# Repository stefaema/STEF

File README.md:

# STEF
Film Transport and Scanning System / Sistema de Transporte y Escaneo Fílmico

## The shells

One `flake.nix`, at the root, and one `flake.lock`. Every module declares what
it needs in its own `module.nix`, as data rather than as an assembled shell, and
the root flake turns those declarations into shells:

```bash
nix develop            # the editor shell
nix develop .#gui      # one module
```

The editor shell is the union: one interpreter carrying every Python import in
the tree, plus `ruff`, `basedpyright` and `clangd`.

A `module.nix` returns an attribute set, every field optional:

| field | what it declares |
| --- | --- |
| `description` | the line `nix eval .#modules.<system>` prints |
| `systems` | where the module builds, both Linux architectures by default |
| `python` | `ps: [ ... ]`, the interpreter's packages |
| `packages` | everything else on `PATH` |
| `env` | variables the shell exports |
| `pythonOverlay` | packages nixpkgs does not carry, added to the interpreter |
| `shell` | a shell taken whole from elsewhere, which `firmware` does |

The interpreter is 3.13, fixed there by `rig`'s CAD wheels being `cp313`.

Every shell exports `STEF_HOME`, pointing at `local/`. `shared.paths` reads it
to decide where config, state and logs go, so a shell that left it unset would
write the log file somewhere nobody thinks to look.

Updating nixpkgs is `nix flake update`, once, at the root.

## Modules

A directory holding a `module.nix` is a module; one without it only groups the
modules below it. The root flake and `ci_cd/discovery.py` walk that same rule,
so one file both declares a module's toolchain and makes it a module. `python -m
ci_cd.run --list` prints what discovery found.

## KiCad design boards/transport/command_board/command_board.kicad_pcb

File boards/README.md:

# Boards
This part of the project will explore the hardware. Specifically, It holds the KiCAD project and Gerber files to both the carrier and driver board.

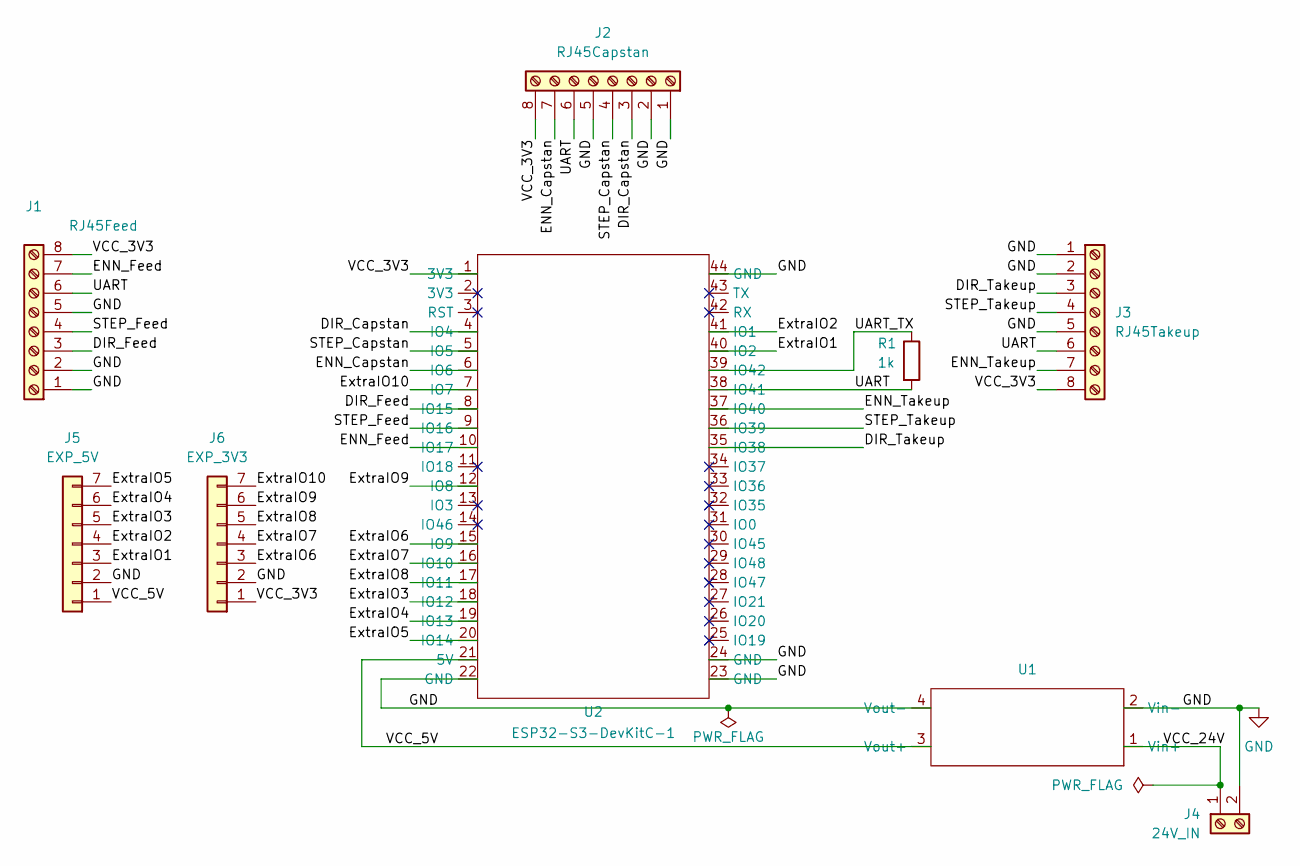
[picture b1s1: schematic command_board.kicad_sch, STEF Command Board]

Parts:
J1: RJ45Feed; PhoenixContact_MC_1,5_8-G-3.5_1x08_P3.50mm_Horizontal
J2: RJ45Capstan; PhoenixContact_MC_1,5_8-G-3.5_1x08_P3.50mm_Horizontal
J3: RJ45Takeup; PhoenixContact_MC_1,5_8-G-3.5_1x08_P3.50mm_Horizontal
J4: 24V_IN; TerminalBlock_RND_205-00287_1x02_P5.08mm_Horizontal
J5: EXP_5V; PinHeader_1x07_P2.54mm_Vertical
J6: EXP_3V3; PinHeader_1x07_P2.54mm_Vertical
R1: 1k; R_Axial_DIN0207_L6.3mm_D2.5mm_P10.16mm_Horizontal
U1: Buck_LM2596; Buck_LM2596_Socketed_2x02
U2: ESP32-S3-DevKitC-1; ESP32-S3-DevKitC-1_Socketed_2x22

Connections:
/DIR_Capstan: J2.3, U2.4 (IO4)
/DIR_Feed: J1.3, U2.8 (IO15)
/DIR_Takeup: J3.3, U2.35 (IO38)
/ENN_Capstan: J2.7, U2.6 (IO6)
/ENN_Feed: J1.7, U2.10 (IO17)
/ENN_Takeup: J3.7, U2.37 (IO40)
/ExtraIO1: J5.3, U2.40 (IO2)
/ExtraIO2: J5.4, U2.41 (IO1)
/ExtraIO3: J5.5, U2.18 (IO12)
/ExtraIO4: J5.6, U2.19 (IO13)
/ExtraIO5: J5.7, U2.20 (IO14)
/ExtraIO6: J6.3, U2.15 (IO9)
/ExtraIO7: J6.4, U2.16 (IO10)
/ExtraIO8: J6.5, U2.17 (IO11)
/ExtraIO9: J6.6, U2.12 (IO8)
/ExtraIO10: J6.7, U2.7 (IO7)
/STEP_Capstan: J2.4, U2.5 (IO5)
/STEP_Feed: J1.4, U2.9 (IO16)
/STEP_Takeup: J3.4, U2.36 (IO39)
/UART: J1.6, J2.6, J3.6, R1.2, U2.38 (IO41)
/UART_TX: R1.1, U2.39 (IO42)
/VCC_3V3: J1.8, J2.8, J3.8, J6.1, U2.1 (3V3)
/VCC_5V: J5.1, U1.3 (Vout+), U2.21 (5V)
/VCC_24V: J4.1, U1.1 (Vin+)
GND: J1.1, J1.2, J1.5, J2.1, J2.2, J2.5, J3.1, J3.2, J3.5, J4.2, J5.2, J6.2, U1.2 (Vin-), U1.4 (Vout-), U2.22 (GND), U2.23 (GND), U2.24 (GND), U2.44 (GND)

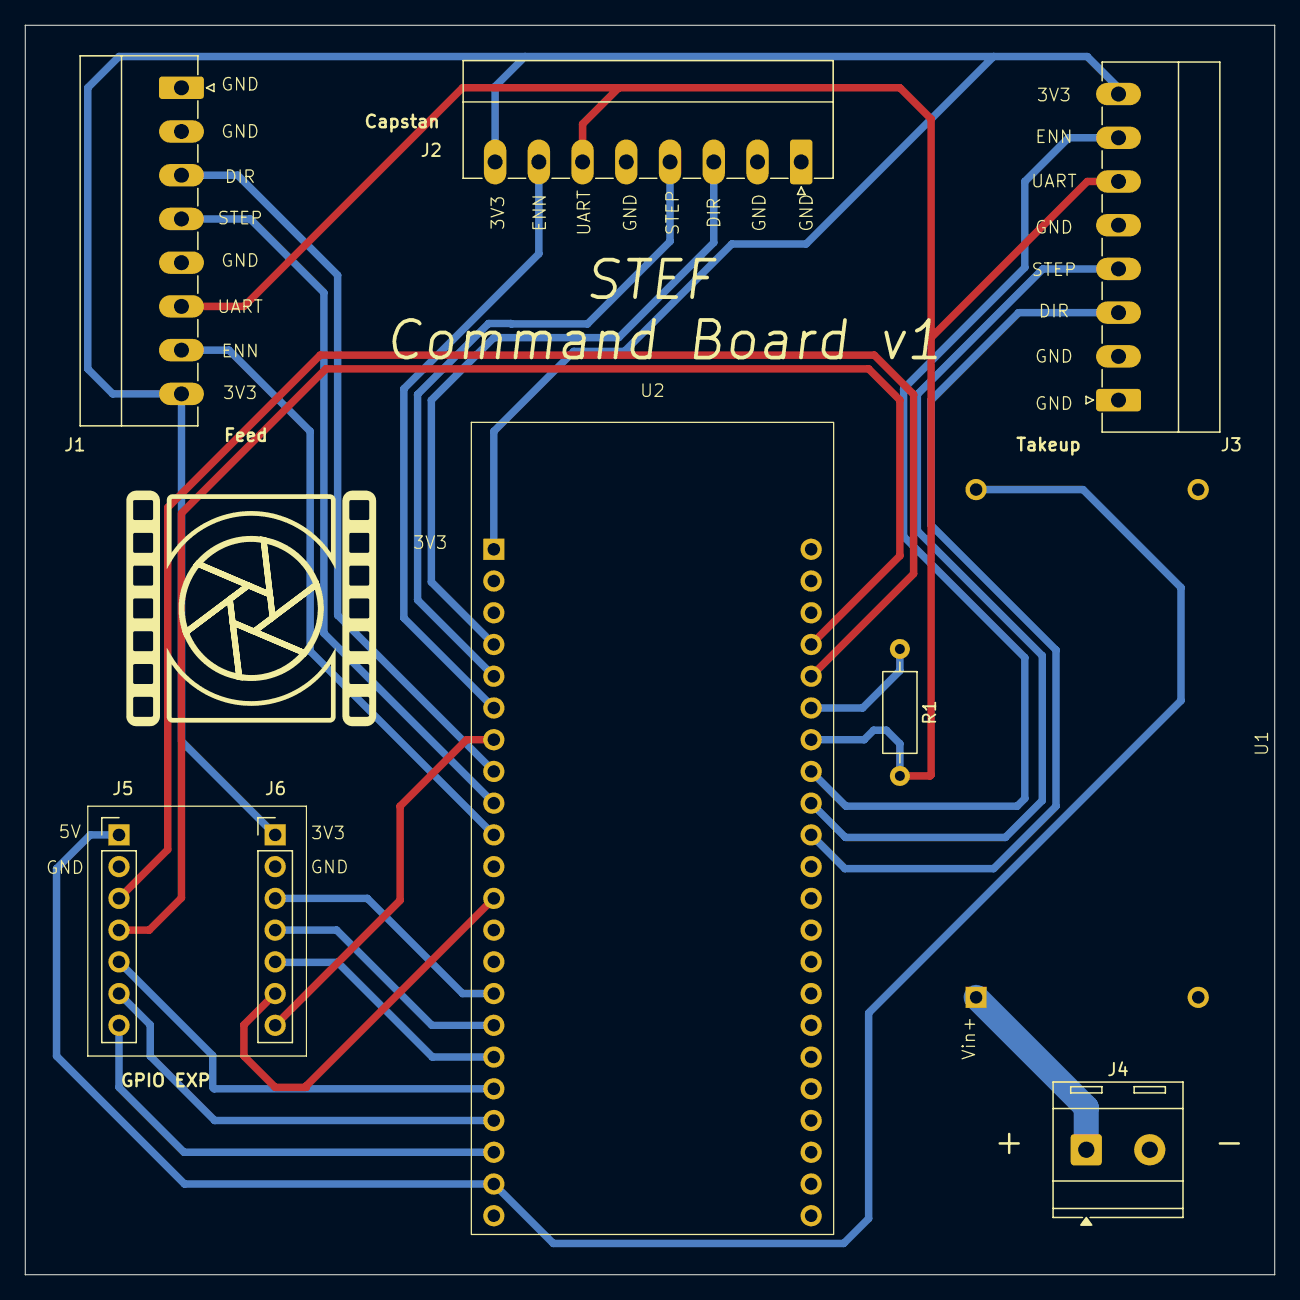
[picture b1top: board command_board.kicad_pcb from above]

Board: 2 copper layers, 100.0 x 100.0 mm, 9 parts (0 on the bottom side), 25 nets.

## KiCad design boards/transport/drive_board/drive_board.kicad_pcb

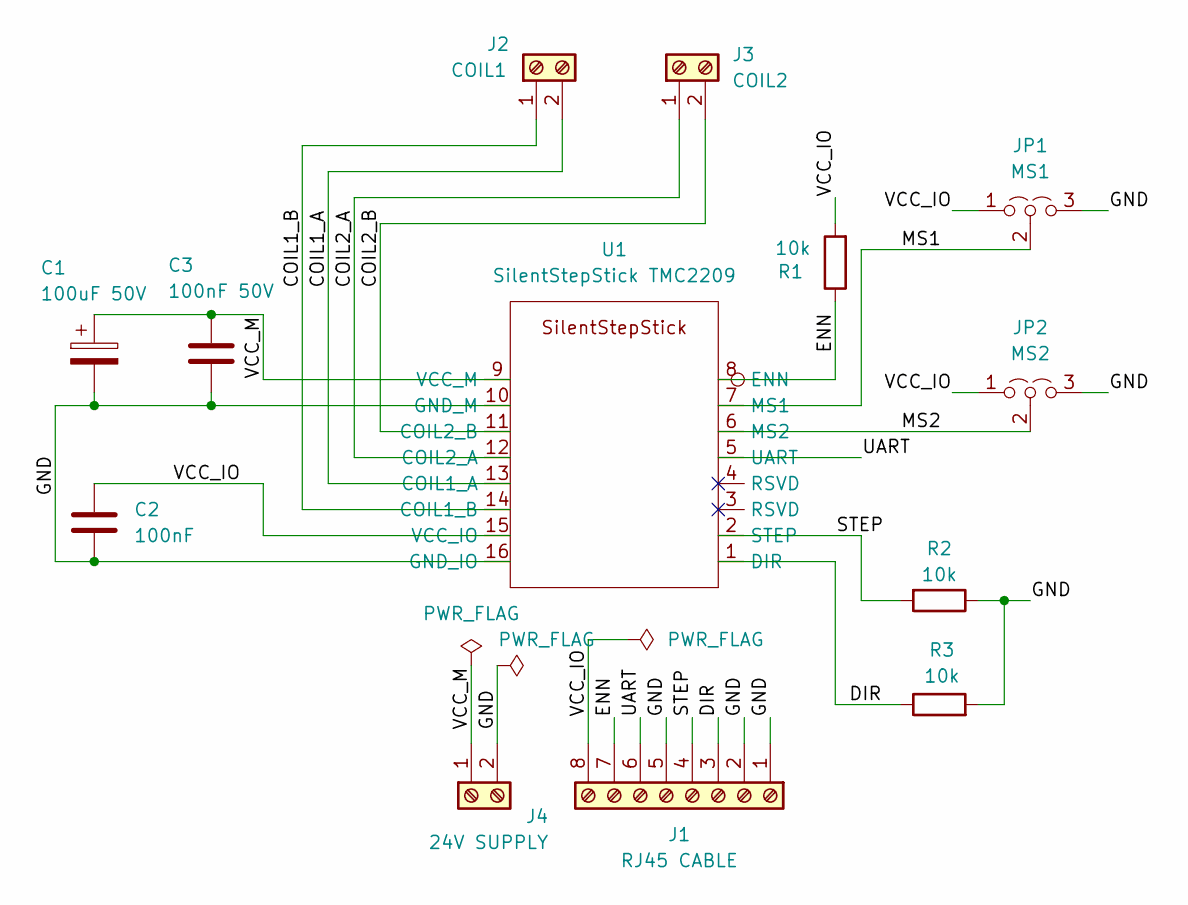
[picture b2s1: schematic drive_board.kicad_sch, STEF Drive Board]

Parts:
C1: 100uF 50V; CP_Radial_D8.0mm_P5.00mm
C2: 100nF; C_Disc_D7.0mm_W2.5mm_P5.00mm
C3: 100nF 50V; C_Disc_D7.0mm_W2.5mm_P5.00mm
J1: RJ45 CABLE; PhoenixContact_MC_1,5_8-G-3.5_1x08_P3.50mm_Horizontal
J2: COIL1; TerminalBlock_RND_205-00287_1x02_P5.08mm_Horizontal
J3: COIL2; TerminalBlock_RND_205-00287_1x02_P5.08mm_Horizontal
J4: 24V SUPPLY; TerminalBlock_RND_205-00287_1x02_P5.08mm_Horizontal
JP1: MS1; PinHeader_1x03_P2.54mm_Vertical
JP2: MS2; PinHeader_1x03_P2.54mm_Vertical
R1, R2, R3: 10k; R_Axial_DIN0207_L6.3mm_D2.5mm_P10.16mm_Horizontal
U1: SilentStepStick TMC2209; SilentStepStick_Socketed_2x08

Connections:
/COIL1_A: J2.2, U1.13 (COIL1_A)
/COIL1_B: J2.1, U1.14 (COIL1_B)
/COIL2_A: J3.1, U1.12 (COIL2_A)
/COIL2_B: J3.2, U1.11 (COIL2_B)
/DIR: J1.3, R3.1, U1.1 (DIR)
/ENN: J1.7, R1.1, U1.8 (ENN)
/GND: C1.2, C2.2, C3.2, J1.1, J1.2, J1.5, J4.2, JP1.3 (B), JP2.3 (B), R2.1, R3.2, U1.10 (GND_M), U1.16 (GND_IO); also elsewhere on the board
/MS1: JP1.2 (C), U1.7 (MS1); also elsewhere on the board
/MS2: JP2.2 (C), U1.6 (MS2)
/STEP: J1.4, R2.2, U1.2 (STEP)
/UART: J1.6, U1.5 (UART)
/VCC_IO: C2.1, J1.8, JP1.1 (A), JP2.1 (A), R1.2, U1.15 (VCC_IO); also elsewhere on the board
/VCC_M: C1.1, C3.1, J4.1, U1.9 (VCC_M)

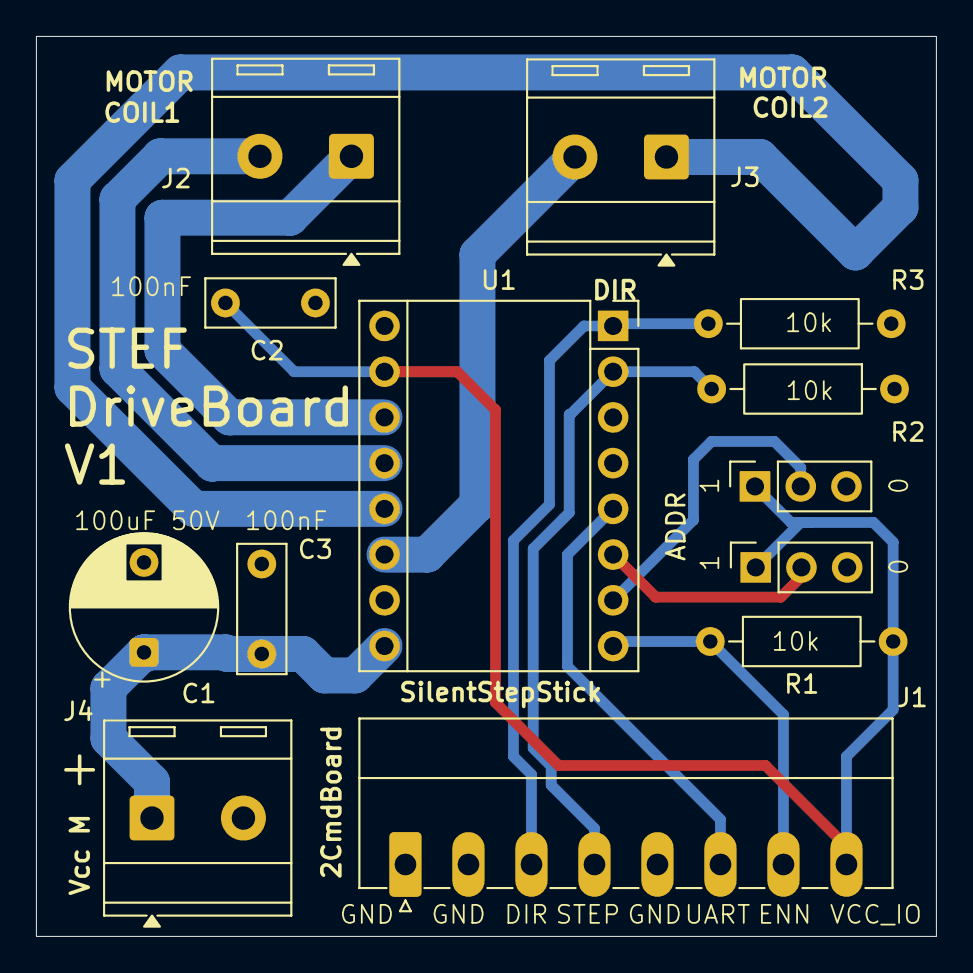
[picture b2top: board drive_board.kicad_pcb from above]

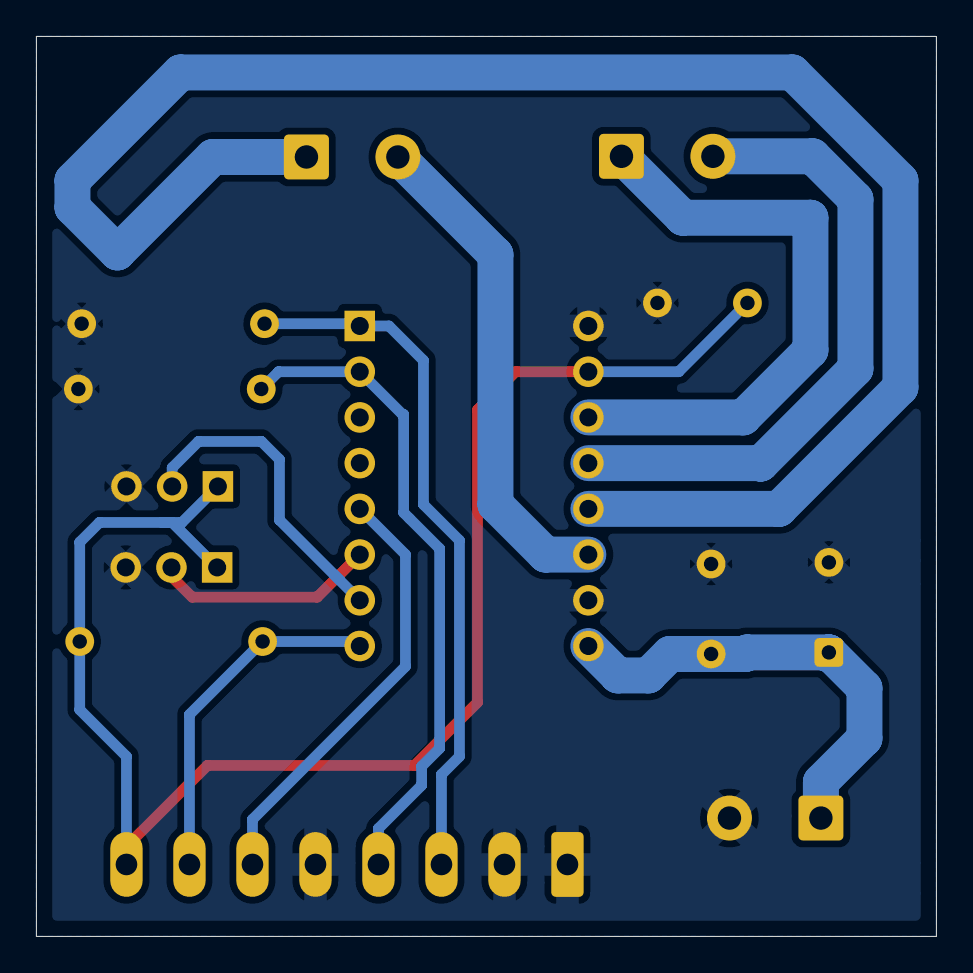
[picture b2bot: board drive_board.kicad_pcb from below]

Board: 2 copper layers, 50.0 x 50.0 mm, 13 parts (8 on the bottom side), 13 nets.

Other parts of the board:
ADDR: MS1; PinHeader_1x03_P2.54mm_Vertical

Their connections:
/GND: ADDR.3 (B); also elsewhere on the board
/MS1: ADDR.2 (C); also elsewhere on the board
/VCC_IO: ADDR.1 (A); also elsewhere on the board
